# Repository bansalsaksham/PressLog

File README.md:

# PressLog — Industrial IoT OEE Downtime Logger

A manufacturing-ready PCB and firmware architecture for capturing machine downtime reasons on a factory floor.

> **Origin:** The original design brief (see `Original Case Study Brief.pdf`) was given as a second-round technical case study during an internship interview process. I completed the full PCB design and firmware architecture independently and am sharing it here as my own project.

> **Status:** PCB design and firmware architecture complete. DRC/ERC clean, Gerbers and BOM generated for fabrication. Not yet physically built/soldered — this repository documents the design and engineering rationale, not a deployed product.

---

## 1. The Problem

OEE (Overall Equipment Effectiveness) is only as good as its data. But capturing downtime reasons at the machine edge is a human-interface problem as much as a software one. The factory floor kills conventional UX.

| Constraint | Root Cause | Why Standard Solutions Fail |
|---|---|---|
| **Gloved hands** | Thick Kevlar + metallic dust make capacitive screens useless | Tablet solutions require bare fingers: 15–30s to glove off/on. Fails the 5-second window. |
| **Patchy Wi-Fi** | VFDs, metal shielding, and RF interference create 2-hour dead zones | Cloud-first designs lose events silently. Operator never knows. OEE has invisible gaps. |
| **5-second window** | Operator moves to the next task seconds after a machine stops | Any UI requiring navigation or multiple confirmations is abandoned. |

## 2. Design Philosophy

- **Physical First** — Six large 30mm illuminated tactile buttons, one per reason code. No menus, no navigation, no scrolling. One press = one logged event, confirmed by an LED flash, an 85dB buzzer, and vibration.
- **Offline First** — Every press is timestamped via a DS3231 RTC and written to 8MB LittleFS flash *before* any network attempt. When Wi-Fi returns, the device silently replays the queue.
- **OEE Ready** — Each event carries `device_id`, `machine_id`, `reason_code`, `operator_uid` (NFC badge tap), UTC timestamp, and a sequence number. Sequence gaps are auto-detected downstream so any connectivity hole is visible to plant management.

## 3. Hardware — Custom 2-Layer PCB (KiCad)

Designed specifically for high-noise industrial environments.

| Engineering Decision | Why It Matters |
|---|---|
| **RC hardware debounce matrix** (10kΩ/0.1µF) on all 6 inputs | Software-only debouncing fails near VFDs and heavy machinery — this prevents ghost button events at the hardware level |
| **Isolated I2C routing for DS3231 RTC** | Routed completely clear of the 150kHz buck converter switching node — prevents inductive noise from corrupting timestamps. If the timestamp is wrong, the offline queue is worthless. |
| **DFM: thermal vias 0.2mm → 0.3mm** | Standard drill size reduces fabrication cost without sacrificing thermal performance |
| **RF-notched board edge** | Lets the ESP32 antenna hang off the fiberglass substrate, preventing signal attenuation |

### Physical Specifications

| Component | Specification |
|---|---|
| Platform | ESP32-S3, dual-core 240MHz |
| Buttons | 6× 30mm illuminated tactile (5N actuation) |
| Connectivity | Wi-Fi 802.11n + BLE 5.0 |
| Offline queue | 8MB LittleFS (~65,000 events) |
| RTC | DS3231, ±2ppm, coin-cell backup |
| Power | 24VDC input + 2000mAh LiPo backup (8h) |
| Identity | PN532 NFC module |

## 4. Firmware Architecture

**Offline-first data flow:**
```
Button Press → RTC Timestamp → Flash Queue (always written first) → Wi-Fi Check → Cloud Sync (batch HTTPS POST)
```

Defense-in-depth: the hardware RC filter kills high-frequency spikes; a 50ms software debounce is the secondary safety net.

```cpp
// Button ISR with secondary 50ms software debounce
void IRAM_ATTR isr_btn_0() {
  uint32_t now = millis();
  if (!pressed[0] && (now - last[0]) > 50) {
    pressed[0] = true;
    last[0] = now;
  }
}

// Queue write — always before network attempt
queueWrite(seq, rtc.now().unixtime(), buttonIdx); // flash first
confirmFeedback(buttonIdx);                       // LED + buzzer + vibration
if (wifiOnline) syncQueue();                       // attempt immediate sync
```

**Event payload schema:**
```json
{
  "device_id": "DL-CNC07-A3",
  "seq": 1042,
  "ts": "2026-04-08T14:22:08Z",
  "ts_source": "rtc",
  "reason_code": "MATERIAL_JAM",
  "reason_label": "Material Jam",
  "operator_uid": "a3f9d82c",
  "machine_id": "CNC-07"
}
```

## 5. Repository Structure

```
├── Hardware_Source/          # KiCad project — schematics + PCB layout
│   ├── ESP32_Core.kicad_sch
│   ├── HMI_IO.kicad_sch
│   ├── Power_Delivery.kicad_sch
│   ├── RTC_SubSystem.kicad_sch
│   └── PressLog_Edge_Node.kicad_pcb / .kicad_pro
├── Manufacturing/            # Fabrication-ready outputs
│   ├── PressLog_Gerbers/
│   └── PressLog_BOM.csv
├── Documentation/            # Renders, design rule reports, app mockups
│   ├── PressLog_Edge_Node.pdf
│   ├── DRC.rpt / ERC.rpt    # Design Rule Check / Electrical Rule Check — board is verified manufacturable
│   ├── PressLog_Front.png / _Back.png / _Side.png
│   └── App Interface Designs.pdf
└── Original Case Study Brief.pdf   # Full original case study writeup
```

## 6. What's Verified vs. Designed-Only

- ✅ Schematic capture across 4 subsystems (ESP32 core, HMI/IO, power delivery, RTC)
- ✅ PCB layout, routed and DRC/ERC clean
- ✅ Gerbers + BOM generated — ready to send to a fab house
- ⬜ Physical assembly / soldering — not yet built
- ⬜ Firmware — architecture and key patterns designed; not yet flashed to hardware

This was a design and engineering reasoning exercise, not a built product. The PCB design itself is real, complete, and manufacturable.

---

**Tools used:** KiCad, ESP32-S3, LittleFS, DS3231 RTC, PN532 NFC

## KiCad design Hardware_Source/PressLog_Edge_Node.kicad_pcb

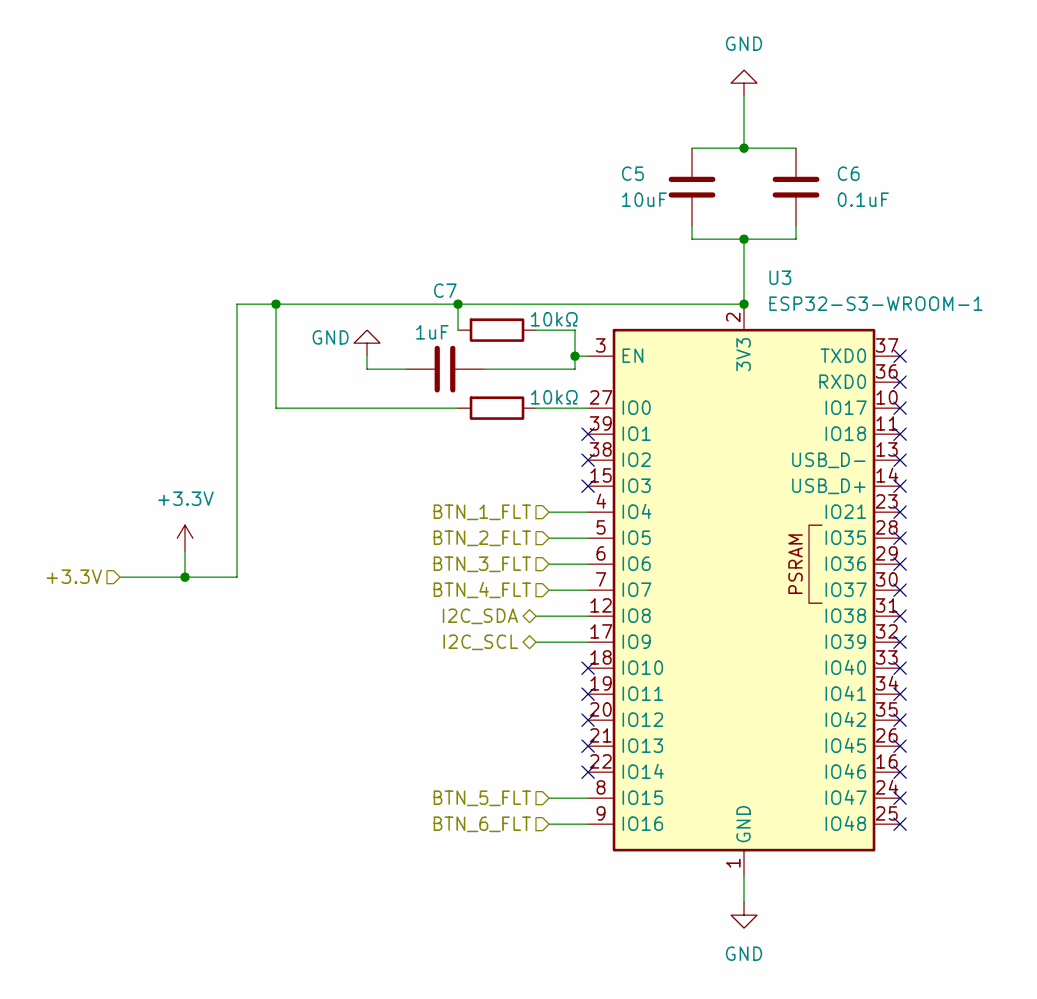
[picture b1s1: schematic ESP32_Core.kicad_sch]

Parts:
C5: 10uF; C_0805_2012Metric
C6: 0.1uF; C_0805_2012Metric
C7: 1uF; C_0805_2012Metric
R1, R2: 10kΩ; R_0805_2012Metric
U3: ESP32-S3-WROOM-1

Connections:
+3.3V: C5.2, C6.2, R1.2, R2.2, U3.2 (3V3); also elsewhere on the board
/BTN_1_FLT: U3.4 (IO4); also elsewhere on the board
/BTN_2_FLT: U3.5 (IO5); also elsewhere on the board
/BTN_3_FLT: U3.6 (IO6); also elsewhere on the board
/BTN_4_FLT: U3.7 (IO7); also elsewhere on the board
/BTN_5_FLT: U3.8 (IO15); also elsewhere on the board
/BTN_6_FLT: U3.9 (IO16); also elsewhere on the board
/I2C_SCL: U3.17 (IO9); also elsewhere on the board
/I2C_SDA: U3.12 (IO8); also elsewhere on the board
GND: C5.1, C6.1, C7.2, U3.1 (GND), U3.40 (GND), U3.41 (GND); also elsewhere on the board
unnamed: C7.1, R1.1, U3.3 (EN)
unnamed: R2.1, U3.27 (IO0)

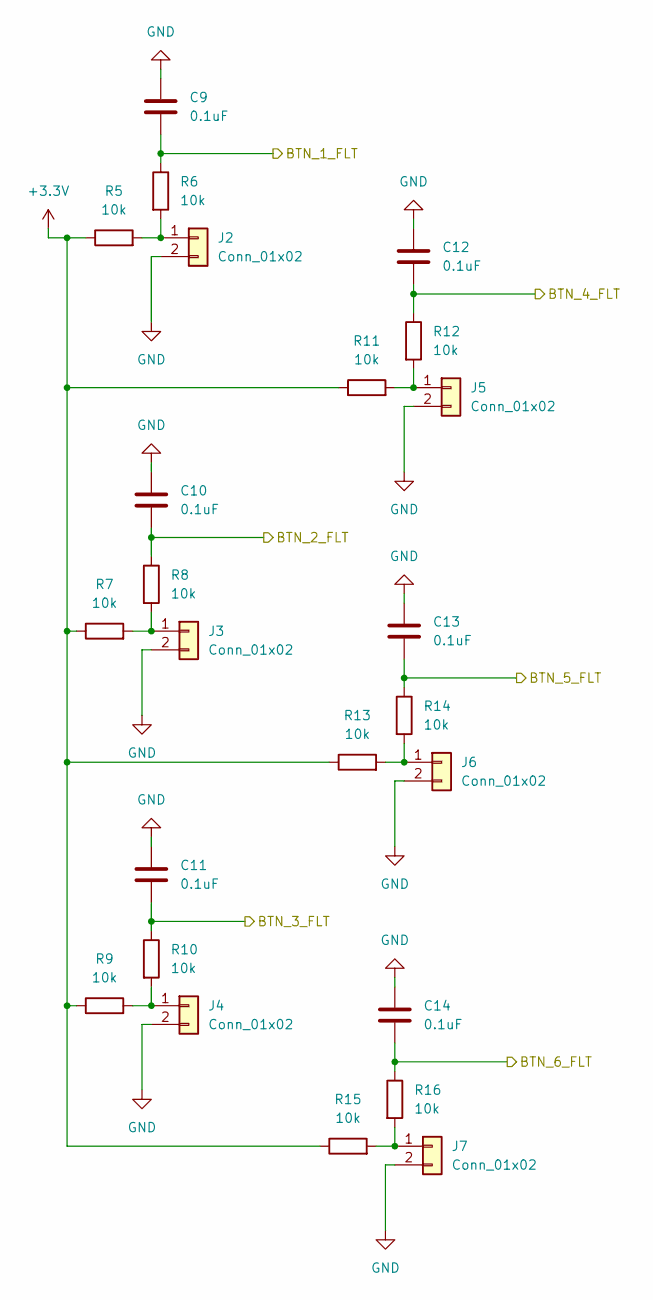
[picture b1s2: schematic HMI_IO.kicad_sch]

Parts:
C9, C10, C11, C12, C13, C14: 0.1uF; C_0805_2012Metric
J2, J3, J4, J5, J6, J7: Conn_01x02; PinHeader_1x02_P2.54mm_Vertical
R5, R6, R7, R8, R9, R10, R11, R12, R13, R14, R15, R16: 10k; R_0805_2012Metric

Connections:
+3.3V: R5.1, R7.1, R9.1, R11.1, R13.1, R15.1; also elsewhere on the board
/BTN_1_FLT: C9.2, R6.1; also elsewhere on the board
/BTN_2_FLT: C10.2, R8.1; also elsewhere on the board
/BTN_3_FLT: C11.2, R10.1; also elsewhere on the board
/BTN_4_FLT: C12.2, R12.1; also elsewhere on the board
/BTN_5_FLT: C13.2, R14.1; also elsewhere on the board
/BTN_6_FLT: C14.2, R16.1; also elsewhere on the board
GND: C9.1, C10.1, C11.1, C12.1, C13.1, C14.1, J2.2, J3.2, J4.2, J5.2, J6.2, J7.2; also elsewhere on the board
unnamed: J2.1, R5.2, R6.2
unnamed: J3.1, R7.2, R8.2
unnamed: J4.1, R9.2, R10.2
unnamed: J5.1, R11.2, R12.2
unnamed: J6.1, R13.2, R14.2
unnamed: J7.1, R15.2, R16.2

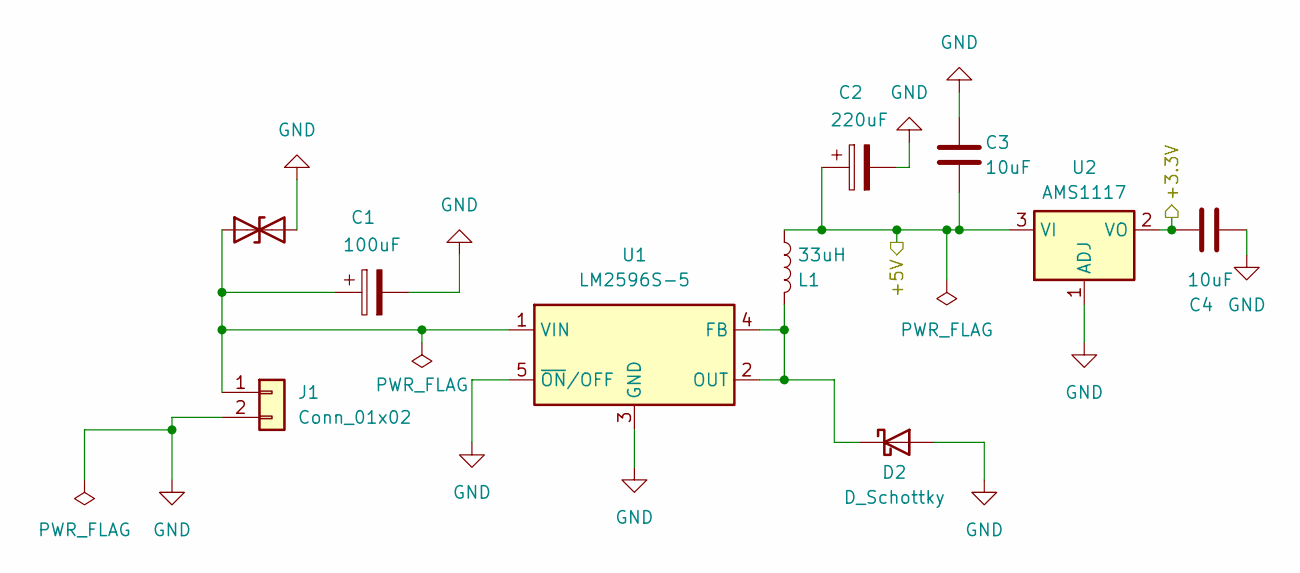
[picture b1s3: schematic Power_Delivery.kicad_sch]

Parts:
C1: 100uF; CP_Radial_D10.0mm_P5.00mm
C2: 220uF; CP_Radial_D10.0mm_P5.00mm
C3, C4: 10uF; C_0805_2012Metric
D1: D_TVS; D_SMA
D2: D_Schottky; D_SMA
J1: Conn_01x02; PinHeader_1x02_P2.54mm_Vertical
L1: 33uH; L_12x12mm_H6mm
U1: LM2596S-5; TO-263-5_TabPin3
U2: AMS1117; SOT-223-3_TabPin2

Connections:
+3.3V: C4.2, U2.2 (VO); also elsewhere on the board
/Power_Delivery/+5V: C2.1, C3.2, L1.2, U2.3 (VI)
GND: C1.2, C2.2, C3.1, C4.1, D1.2 (A2), D2.2 (A), J1.2, U1.3 (GND), U1.5 (~ON/OFF), U2.1 (ADJ); also elsewhere on the board
unnamed: C1.1, D1.1 (A1), J1.1, U1.1 (VIN)
unnamed: D2.1 (K), L1.1, U1.2 (OUT), U1.4 (FB)

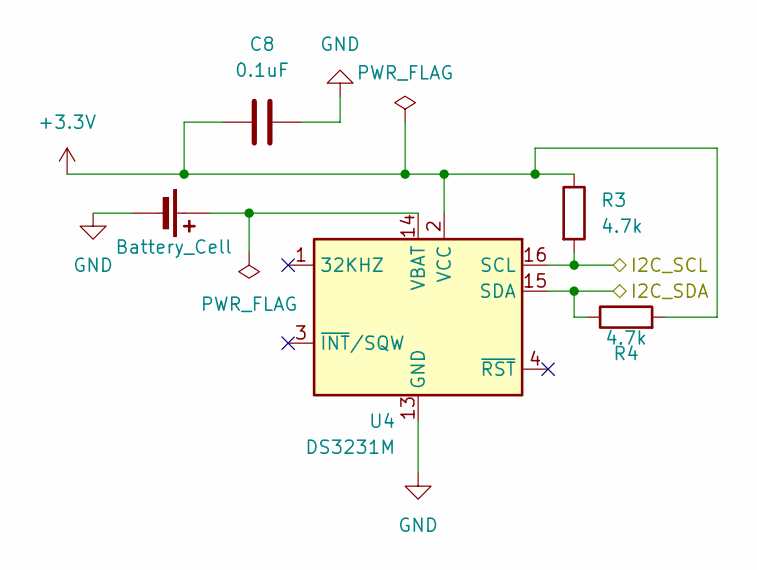
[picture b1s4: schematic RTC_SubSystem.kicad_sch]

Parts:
BT1: Battery_Cell; BatteryHolder_Keystone_1058_1x2032
C8: 0.1uF; C_0805_2012Metric
R3, R4: 4.7k; R_0805_2012Metric
U4: DS3231M; SOIC-16W_7.5x10.3mm_P1.27mm

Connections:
+3.3V: C8.2, R3.1, R4.2, U4.2 (VCC); also elsewhere on the board
/I2C_SCL: R3.2, U4.16 (SCL); also elsewhere on the board
/I2C_SDA: R4.1, U4.15 (SDA); also elsewhere on the board
GND: BT1.2 (-), C8.1, U4.5 (GND), U4.6 (GND), U4.7 (GND), U4.8 (GND), U4.9 (GND), U4.10 (GND), U4.11 (GND), U4.12 (GND), U4.13 (GND); also elsewhere on the board
unnamed: BT1.1 (+), U4.14 (VBAT)

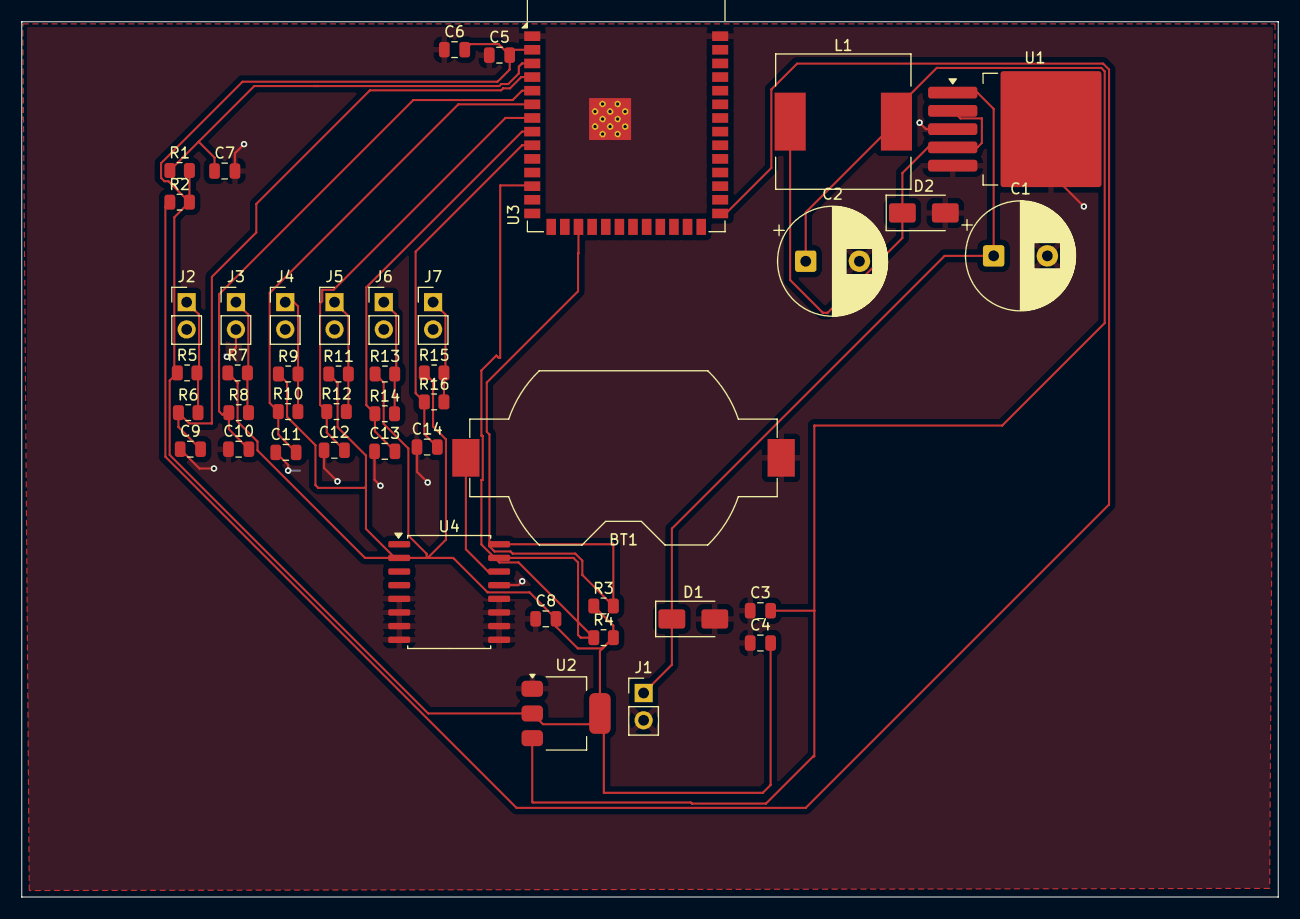
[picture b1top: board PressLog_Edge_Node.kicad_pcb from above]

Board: 2 copper layers, 117.0 x 81.5 mm, 45 parts (0 on the bottom side), 22 nets.

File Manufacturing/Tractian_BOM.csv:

"Reference","Qty","Value","DNP","Exclude from BOM","Exclude from Board","Footprint","Datasheet"
"BT1","1","Battery_Cell","","","","Battery:BatteryHolder_Keystone_1058_1x2032","~"
"C1","1","100uF","","","","Capacitor_THT:CP_Radial_D10.0mm_P5.00mm","~"
"C2","1","220uF","","","","Capacitor_THT:CP_Radial_D10.0mm_P5.00mm","~"
"C3,C4,C5","3","10uF","","","","Capacitor_SMD:C_0805_2012Metric","~"
"C6,C8,C9,C10,C11,C12,C13,C14","8","0.1uF","","","","Capacitor_SMD:C_0805_2012Metric","~"
"C7","1","1uF","","","","Capacitor_SMD:C_0805_2012Metric","~"
"D1","1","D_TVS","","","","Diode_SMD:D_SMA","~"
"D2","1","D_Schottky","","","","Diode_SMD:D_SMA","~"
"J1,J2,J3,J4,J5,J6,J7","7","Conn_01x02","","","","Connector_PinHeader_2.54mm:PinHeader_1x02_P2.54mm_Vertical","~"
"L1","1","33uH","","","","Inductor_SMD:L_12x12mm_H6mm","~"
"R1,R2","2","10kΩ","","","","Resistor_SMD:R_0805_2012Metric","~"
"R3,R4","2","4.7k","","","","Resistor_SMD:R_0805_2012Metric","~"
"R5,R6,R7,R8,R9,R10,R11,R12,R13,R14,R15,R16","12","10k","","","","Resistor_SMD:R_0805_2012Metric","~"
"U1","1","LM2596S-5","","","","Package_TO_SOT_SMD:TO-263-5_TabPin3","http://www.ti.com/lit/ds/symlink/lm2596.pdf"
"U2","1","AMS1117","","","","Package_TO_SOT_SMD:SOT-223-3_TabPin2","http://www.advanced-monolithic.com/pdf/ds1117.pdf"
"U3","1","ESP32-S3-WROOM-1","","","","RF_Module:ESP32-S3-WROOM-1","https://www.espressif.com/sites/default/files/documentation/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"
"U4","1","DS3231M","","","","Package_SO:SOIC-16W_7.5x10.3mm_P1.27mm","http://datasheets.maximintegrated.com/en/ds/DS3231.pdf"

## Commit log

2026-06-21 Rename Tractian_Back.png to PressLog_Back.png
2026-06-21 Rename Tractian_Edge_Node.pdf to PressLog_Edge_Node.pdf
2026-06-21 Rename Tractian_Front.png to PressLog_Front.png
2026-06-21 Rename Tractian_Side.png to PressLog_Side.png
2026-06-21 Rename Tractian_Edge_Node.kicad_pcb to PressLog_Edge_Node.kicad_pcb
2026-06-21 Rename Tractian_Edge_Node.kicad_prl to PressLog_Edge_Node.kicad_prl
2026-06-21 Rename Tractian_Edge_Node.kicad_pro to PressLog_Edge_Node.kicad_pro
2026-06-21 Rename Tractian_Edge_Node.kicad_sch to PressLog_Edge_Node.kicad_sch
2026-06-21 Rename Tractian_BOM.csv to PressLog_BOM.csv
2026-06-21 Rename Traction Case Study.pdf to Original Case Study Brief.pdf
